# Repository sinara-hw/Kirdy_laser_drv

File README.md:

# Kirdy

Low Noise Precision Laser Diode Driver with Built-in TEC Temperature Controller  

## Power Input
| Parameter | Min | Typical | Max | Unit | Condition |
| --- | --- | --- | --- | --- | ---|
| Input Voltage | | 12 | | V | |
| Input Current | | | 2 | A|
| PoE Standard | |  PoE+ (802.3at) | | |

Note: TEC Output Current should be limited to ±2A when it is being powered via PoE(802.3af). Otherwise, Kirdy may malfunction.

## Laser Diode Driver
### Current Source Controller  
| Parameter | Min | Typical | Max | Unit | Condition |
| --- | --- | --- | --- | --- | ---| 
| Resolution | | 0.292 | | uA |
| Control Range| | | 307.2 | mA | |
| Current Limit | | 319. | | mA| |
| Compliance voltage | | > 4.928 | | V | |   
| Current Noise (@ 1 kHz) | | < 300 || pA / rt(Hz) | @ DC Bias: 300 mA, Load: 10 Ω Load|
| RMS Noise(10 Hz - 1 MHz) || < 300 | | nA | @ DC Bias: 300 mA, Load: 10 Ω Load| 
| Temperature Coefficient | | ±1 | | ppm/°C | @ DC Bias: 50 mA. Tested Temperature Range: 43-56 °C |

### Photodiode Input
| Parameter | Min | Typical | Max | Unit | Condition |
| --- | --- | --- | --- | --- | ---|
| Photocurrent Range | 0 | | 3.0 | mA | |
| Photocurrent Resolution | | 0.8 | | uA | |
| Bandwidth (-3 dB) | | 500 | | Hz | |

Note1: Circuit may be damaged if photodiode input current exceeds 3.0 mA. User can modify the circuit and reprogram the photodiode current monitor range via the given driver.

Note2: Photodiode operates in photovoaic mode.

### Low Frequency Modulation Input
| Parameter | Min | Typical | Max | Unit | Condition |
| --- | --- | --- | --- | --- | ---|
| Input Voltage | -1.0 | | 1.0 | V | |
| Input Impedance | | 50 or 43.4k | | ohm | Depends on Termination Switch Position |
| Bandwidth (-3 dB) | | 18 | | MHz | @Modulation Depth: 25 mA/V, Input : 1 Vp-p, DC Bias: 150 mA |

Note: Low Frequency Modulation Input can accept DC input to impose a DC offset to the output current.

## TEC Temperature Controller
### TEC Current Output
| Parameter | Min | Typical | Max | Unit | Condition |
| --- | --- | --- | --- | --- | ---|
| Resolution | | 22.9 | | uA | |
| Control Range (Powered via 12 V Barrel Jack) | -3.0 | | 3.0 | A | With Active Cooling |
| Control Range (Powered via PoE(802.3af)) | -2.0 | | 2.0 | A | |
| Compliance Voltage | | 4.3 |  | V | |
| Voltage Reading Resolution | | 3.22 | | mV | |
| Current Reading Resolution | |  2.0 | | mA | |

### TEC Voltage and Current Limit
| Parameter | Min | Typical | Max | Unit | Condition |
| --- | --- | --- | --- | --- | ---|
| Voltage Limit Settable Range| 0 | | 4.3 | V | |
| Voltage Limit Resolution | | 3.14 | | mV | |
| Current Limit Settable Range | -3.0 | | 3.0 | A | |
| Current Limit Resolution | |  1.57 | | mA | |

### NTC Thermistor Sensor
| Parameter | Min | Typical | Max | Unit | Condition |
| --- | --- | --- | --- | --- | ---|
| Resolution | | 0.01 | | mK | With 10 kohm NTC with 3950 B-Constant, 25°C T0 |
| Sampling Rate | | 16.67 | > 1k | Hz | |

Note: Actual Sampling Rate subjects to device operating conditions.

### Digital PID Temperature Controller
| Parameter | Min | Typical | Max | Unit | Condition |
| --- | --- | --- | --- | --- | ---|
| Temperature Stability | | < 1| | mk | Using supplied Kirdy Adapter with its copper plate installed. PID Parameters are obtained from Kirdy Autotune Algorithm. |

Note: Actual Temperature Stability subjects to the ambient environment conditions.

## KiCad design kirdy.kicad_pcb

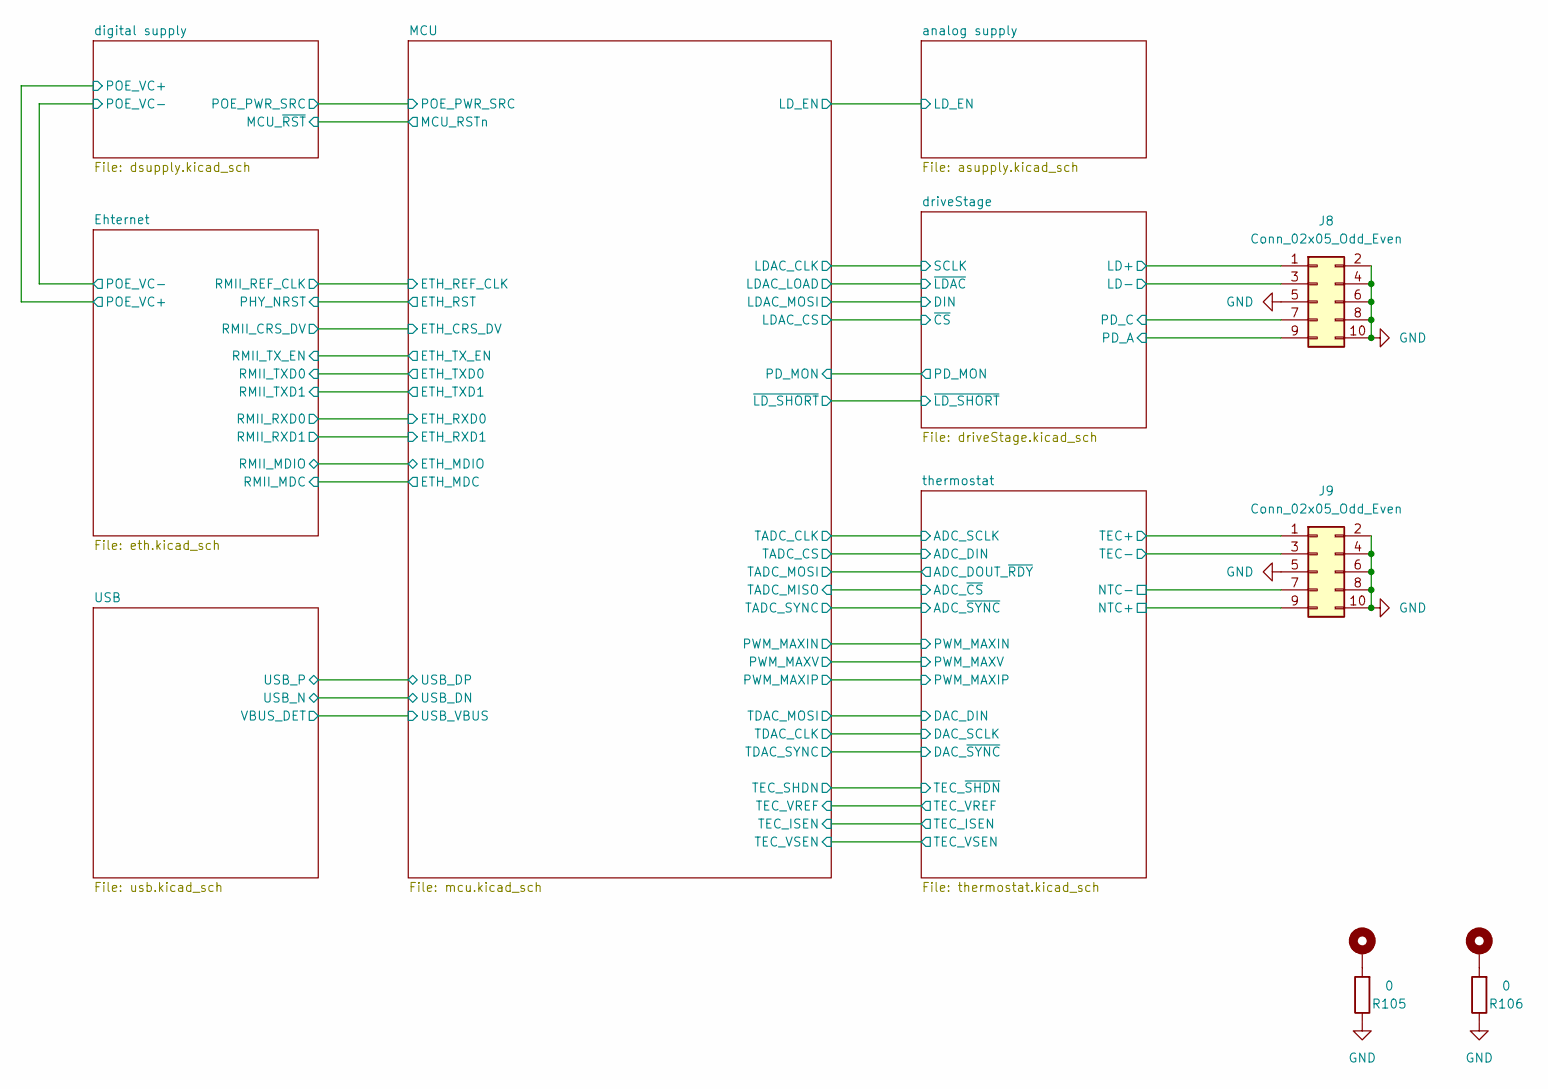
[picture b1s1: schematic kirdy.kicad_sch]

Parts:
H1, H2: MountingHole_Pad; MountingHole_2.7mm_M2.5_Pad_Via
J8, J9: Conn_02x05_Odd_Even; PinHeader_2x05_P2.54mm_Vertical_SMD; MFR_PN 3020-10-0300-00
R105, R106: 0; R_0603_1608Metric; MFR_PN RMCF0603ZT0R00

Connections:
+3.3VA: J8.7; also elsewhere on the board
+8V: J8.1; also elsewhere on the board
/driveStage/LD-: J8.3; also elsewhere on the board
/driveStage/PD_A: J8.9; also elsewhere on the board
/thermostat/NTC+: J9.9; also elsewhere on the board
/thermostat/NTC-: J9.7; also elsewhere on the board
/thermostat/TEC+: J9.1; also elsewhere on the board
/thermostat/TEC-: J9.3; also elsewhere on the board
GND: J8.2, J8.4, J8.5, J8.6, J8.8, J8.10, J9.2, J9.4, J9.5, J9.6, J9.8, J9.10, R105.1, R106.1; also elsewhere on the board
unnamed: H1.1, R105.2
unnamed: H2.1, R106.2

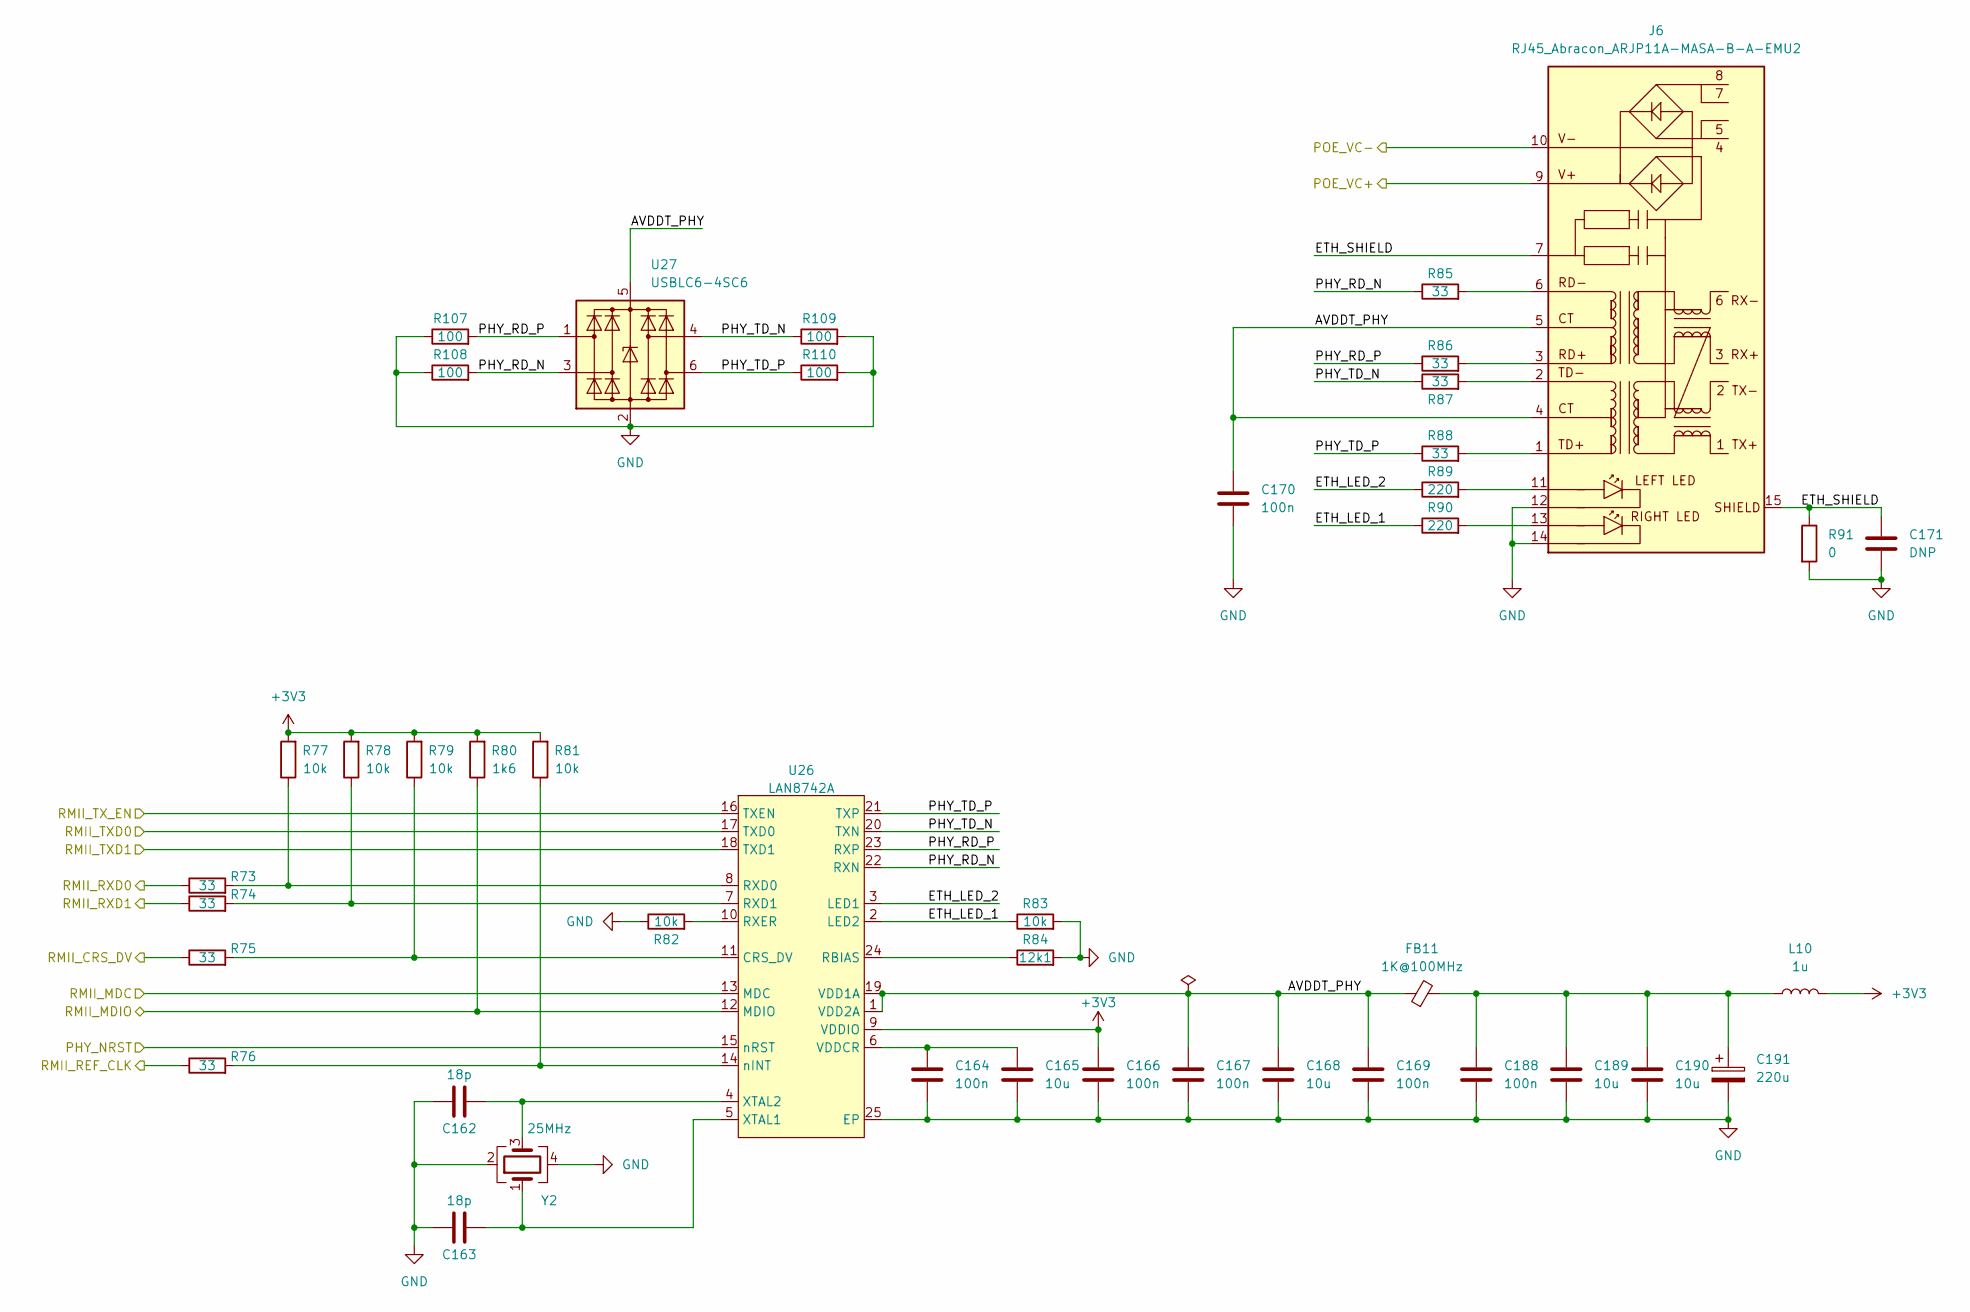
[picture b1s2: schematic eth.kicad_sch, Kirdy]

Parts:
C162, C163: 18p; C_0603_1608Metric; MFR_PN 0603N180J500CT
C164, C166, C167, C169, C170, C188: 100n; C_0603_1608Metric; MFR_PN CL10B104KB8NNWC
C165, C168, C189, C190: 10u; C_0805_2012Metric; MFR_PN CL21B106KOQNNNG
C171: DNP; C_1206_3216Metric; MFR_PN 12067C472KAT2A
C191: 220u; CP_EIA-7343-15_Kemet-W; MFR_PN T491D227K016AT
FB11: 1K@100MHz; L_1210_3225Metric; MFR_PN FBMH3225HM102NT
J6: RJ45_Abracon_ARJP11A-MASA-B-A-EMU2; RJ45_Abracon_ARJP11A-MA_Horizontal; MFR_PN ARJP11A-MASA-B-A-EMU2
L10: 1u; L_1008_2520Metric; MFR_PN DFE252012F-1R0M=P2
R73, R74, R75, R76, R85, R86, R87, R88: 33; R_0603_1608Metric; MFR_PN RC0603FR-0733RL
R77, R78, R79, R81, R82, R83: 10k; R_0603_1608Metric; MFR_PN RNCP0603FTD10K0
R80: 1k6; R_0603_1608Metric; MFR_PN RT0603FRE071K6L
R84: 12k1; R_0603_1608Metric; MFR_PN RNCP0603FTD12K1
R89, R90: 220; R_0603_1608Metric; MFR_PN WR06X2200FTL
R91: 0; R_0603_1608Metric; MFR_PN RMCF0603ZT0R00
R107, R108, R109, R110: 100; R_0603_1608Metric; MFR_PN RT0603FRE07300RL
U26: LAN8742A; QFN-24-1EP_4x4mm_P0.5mm_EP2.6x2.6mm; MFR_PN LAN8742A-CZ
U27: USBLC6-4SC6; SOT-23-6; MFR_PN USBLC6-4SC6Y
Y2: 25MHz; Crystal_SMD_2016-4Pin_2.0x1.6mm; MFR_PN FA-128 25.0000MF10Z-AC3

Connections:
+3V3: C166.1, L10.2, R77.2, R78.2, R79.2, R80.2, R81.2, U26.9 (VDDIO); also elsewhere on the board
/Ehternet/AVDDT_PHY: C167.1, C168.1, C169.1, C170.1, FB11.1, J6.4 (CT), J6.5 (CT), U26.1 (VDD2A), U26.19 (VDD1A), U27.5 (VBUS)
/Ehternet/ETH_LED_1: R83.1, R90.1, U26.2 (LED2)
/Ehternet/ETH_LED_2: R89.1, U26.3 (LED1)
/Ehternet/ETH_SHIELD: C171.1, J6.7, J6.15 (SHIELD), R91.1
/Ehternet/PHY_NRST: U26.15 (nRST); also elsewhere on the board
/Ehternet/PHY_RD_N: R85.1, R108.2, U26.22 (RXN), U27.3 (I/O2)
/Ehternet/PHY_RD_P: R86.1, R107.2, U26.23 (RXP), U27.1 (I/O1)
/Ehternet/PHY_TD_N: R87.1, R109.1, U26.20 (TXN), U27.4 (I/O3)
/Ehternet/PHY_TD_P: R88.1, R110.1, U26.21 (TXP), U27.6 (I/O4)
/Ehternet/POE_VC+: J6.9 (V+); also elsewhere on the board
/Ehternet/POE_VC-: J6.10 (V-); also elsewhere on the board
/Ehternet/RMII_CRS_DV: R75.1; also elsewhere on the board
/Ehternet/RMII_MDC: U26.13 (MDC); also elsewhere on the board
/Ehternet/RMII_MDIO: R80.1, U26.12 (MDIO); also elsewhere on the board
/Ehternet/RMII_REF_CLK: R76.1; also elsewhere on the board
/Ehternet/RMII_RXD0: R73.1; also elsewhere on the board
/Ehternet/RMII_RXD1: R74.1; also elsewhere on the board
/Ehternet/RMII_TXD0: U26.17 (TXD0); also elsewhere on the board
/Ehternet/RMII_TXD1: U26.18 (TXD1); also elsewhere on the board
/Ehternet/RMII_TX_EN: U26.16 (TXEN); also elsewhere on the board
GND: C162.1, C163.1, C164.2, C165.2, C166.2, C167.2, C168.2, C169.2, C170.2, C171.2, C188.2, C189.2, C190.2, C191.2, J6.12 (LLED-), J6.14 (RLED-), R82.1, R83.2, R84.2, R91.2, R107.1, R108.1, R109.2, R110.2, U26.25 (EP), U27.2 (GND), Y2.2, Y2.4; also elsewhere on the board
unnamed: C162.2, U26.4 (XTAL2), Y2.3
unnamed: C163.2, U26.5 (XTAL1), Y2.1
unnamed: C164.1, C165.1, U26.6 (VDDCR)
unnamed: C188.1, C189.1, C190.1, C191.1, FB11.2, L10.1
unnamed: J6.1 (TD+), R88.2
unnamed: J6.2 (TD-), R87.2
unnamed: J6.3 (RD+), R86.2
unnamed: J6.6 (RD-), R85.2
unnamed: J6.11 (LLED+), R89.2
unnamed: J6.13 (RLED+), R90.2
unnamed: R73.2, R77.1, U26.8 (RXD0)
unnamed: R74.2, R78.1, U26.7 (RXD1)
unnamed: R75.2, R79.1, U26.11 (CRS_DV)
unnamed: R76.2, R81.1, U26.14 (nINT)
unnamed: R82.2, U26.10 (RXER)
unnamed: R84.1, U26.24 (RBIAS)

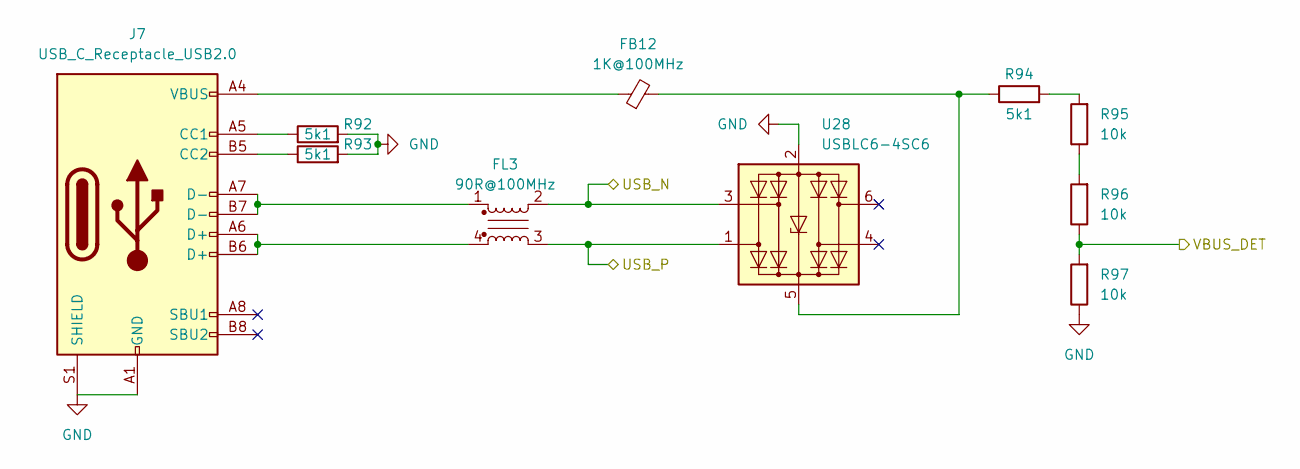
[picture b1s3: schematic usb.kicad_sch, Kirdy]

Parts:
FB12: 1K@100MHz; L_1210_3225Metric; MFR_PN FBMH3225HM102NT
FL3: 90R@100MHz; L_CommonModeChoke_Coilcraft_0603USB; MFR_PN 0603USB-222MLC
J7: USB_C_Receptacle_USB2.0; USB_C_Receptacle_HRO_TYPE-C-31-M-12; MFR_PN TYPE-C-31-M-12
R92, R93, R94: 5k1; R_0603_1608Metric; MFR_PN RMCF0603FT5K10
R95, R96, R97: 10k; R_0603_1608Metric; MFR_PN RNCP0603FTD10K0
U28: USBLC6-4SC6; SOT-23-6; MFR_PN USBLC6-4SC6Y

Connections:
/MCU/USB_DN: FL3.2, U28.3 (I/O2); also elsewhere on the board
/MCU/USB_DP: FL3.3, U28.1 (I/O1); also elsewhere on the board
/MCU/USB_VBUS: R96.1, R97.2; also elsewhere on the board
GND: J7.A1 (GND), J7.A12 (GND), J7.B1 (GND), J7.B12 (GND), J7.S1 (SHIELD), R92.2, R93.2, R97.1, U28.2 (GND); also elsewhere on the board
unnamed: FB12.1, J7.A4 (VBUS), J7.A9 (VBUS), J7.B4 (VBUS), J7.B9 (VBUS)
unnamed: FB12.2, R94.1, U28.5 (VBUS)
unnamed: FL3.1, J7.A7 (D-), J7.B7 (D-)
unnamed: FL3.4, J7.A6 (D+), J7.B6 (D+)
unnamed: J7.A5 (CC1), R92.1
unnamed: J7.B5 (CC2), R93.1
unnamed: R94.2, R95.2
unnamed: R95.1, R96.2

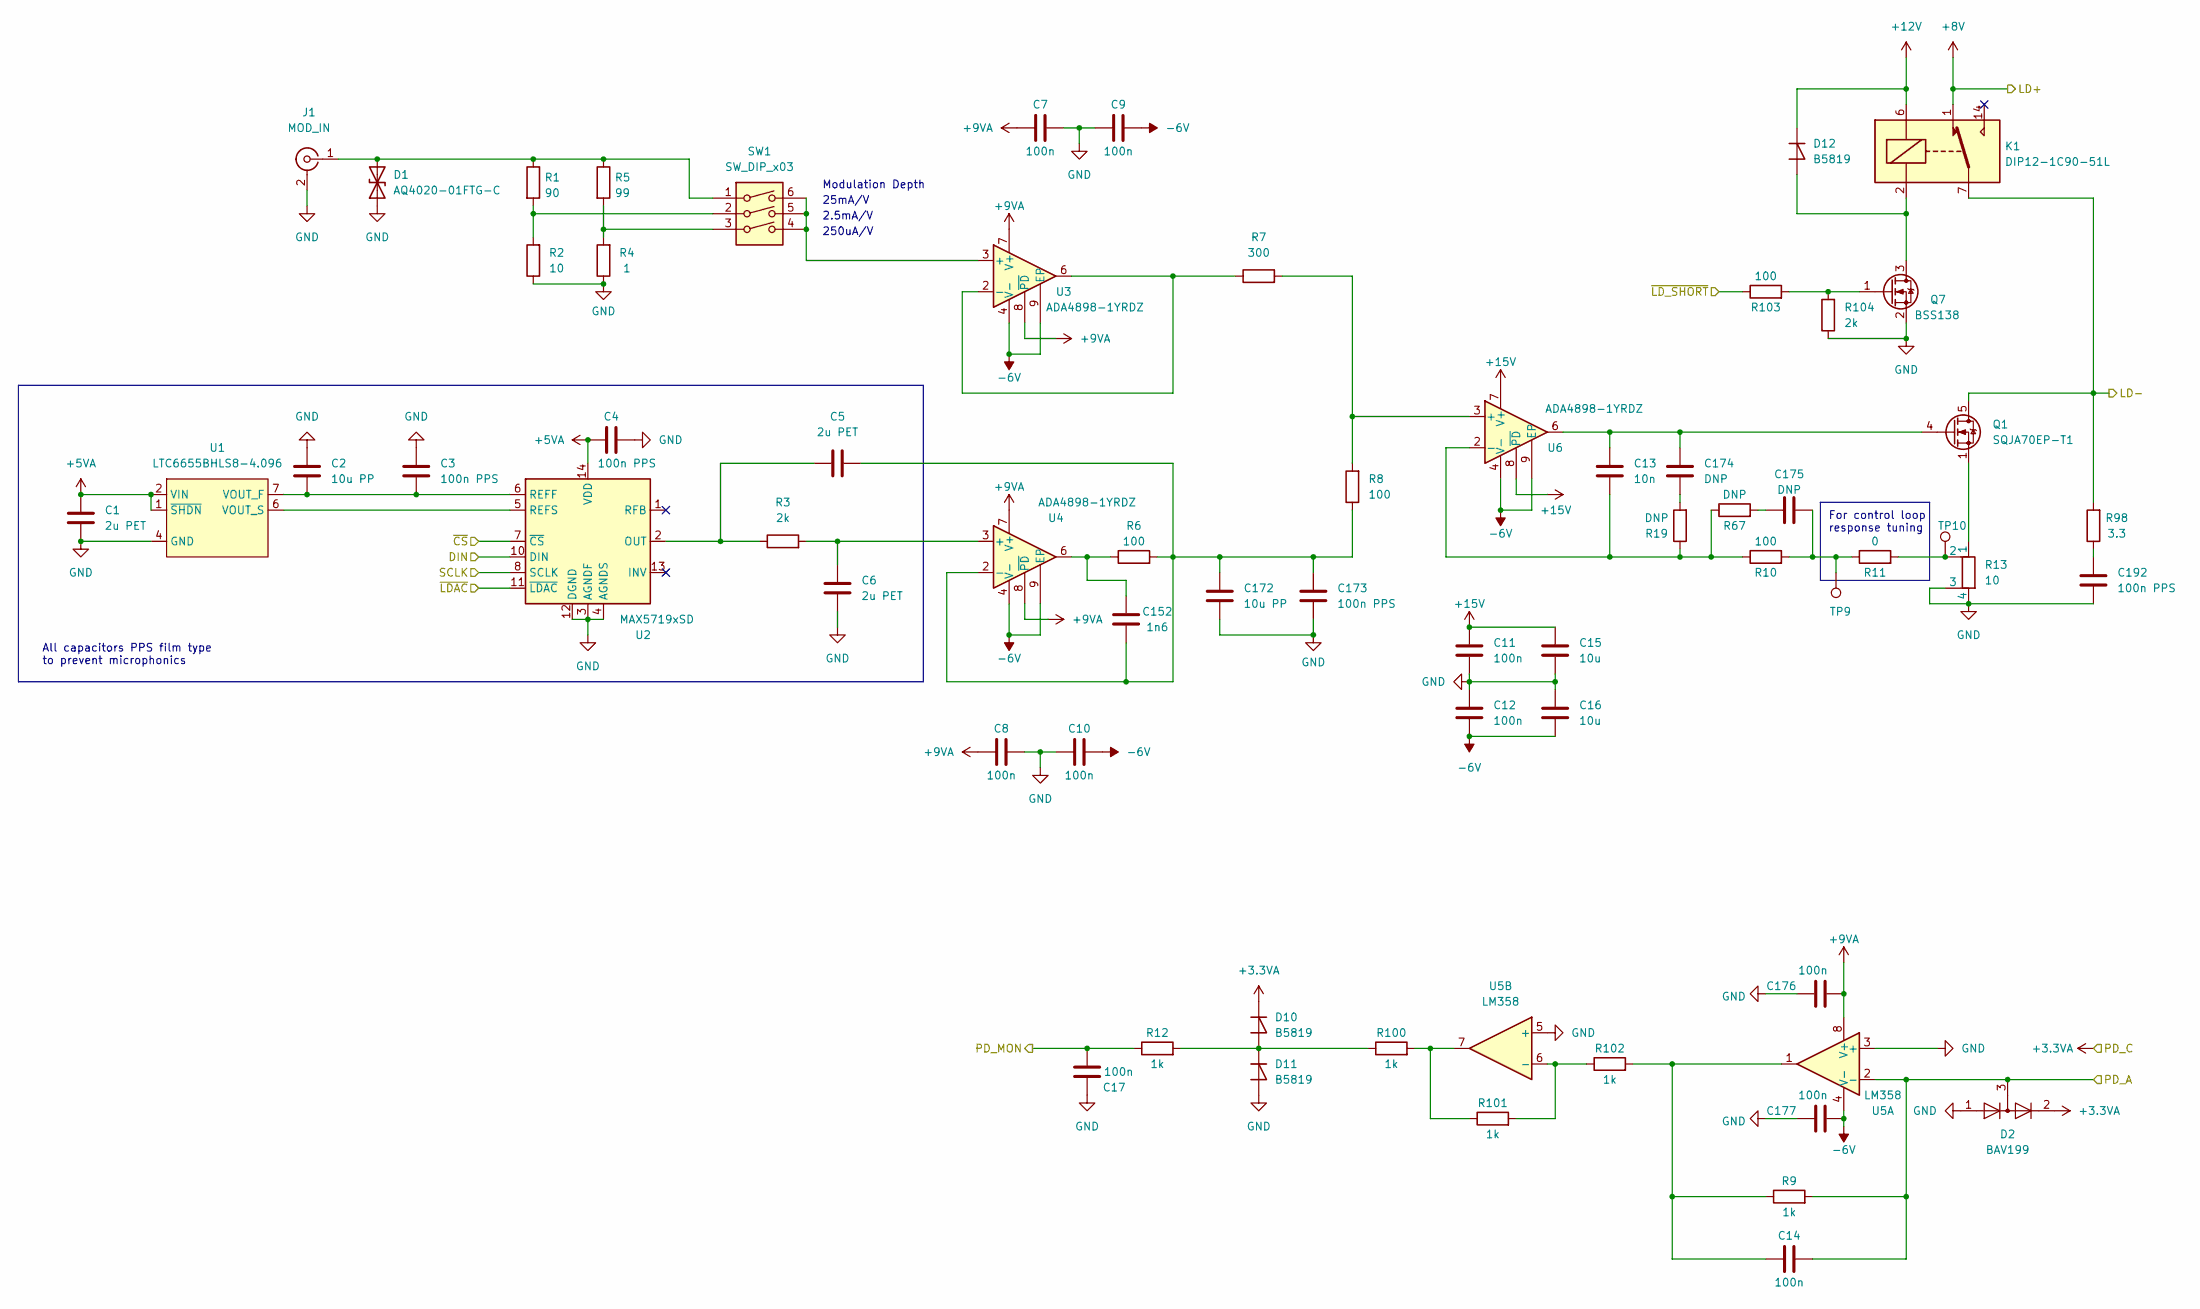
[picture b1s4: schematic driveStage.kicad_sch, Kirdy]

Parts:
C1, C5, C6: 2u PET; C_1812_4532Metric; MFR_PN 35MU225MC14532
C2, C172: 10u PP; C_1812_4532Metric; MFR_PN 16MU106MC44532
C3, C4, C173, C192: 100n PPS; C_1210_3225Metric; MFR_PN ECH-U1C104JX5
C7, C8, C9, C10, C11, C12, C17, C176, C177: 100n; C_0603_1608Metric; MFR_PN CL10B104KB8NNWC
C13: 10n; C_0603_1608Metric; MFR_PN 0603B103K500CT
C14: 100n; C_0603_1608Metric; MFR_PN GCM1885C1H162FA16D
C15, C16: 10u; C_0805_2012Metric; MFR_PN CL21B106KOQNNNG
C152: 1n6; C_0603_1608Metric; MFR_PN GCM1885C1H162FA16D
C174, C175: DNP; C_0603_1608Metric
D1: AQ4020-01FTG-C; D_SOD-323; MFR_PN AQ4020-01FTG-C
D2: BAV199; SOT-23; MFR_PN BAV199W-7
D10, D11, D12: B5819; D_SOD-323; MFR_PN B5819WS-TP
J1: MOD_IN; SMA_Amphenol_132203-12_Horizontal; MFR_PN 132203-12
K1: DIP12-1C90-51L; Relay_StandexMeder_DIP_LowProfile
Q1: SQJA70EP-T1; TDSON-8-1; MFR_PN SQJA70EP-T1_GE3
Q7: BSS138; SOT-23; MFR_PN BSS138W-TP
R1: 90; R_0603_1608Metric
R2: 10; R_0603_1608Metric; MFR_PN RT0603BRD0710RL
R3, R104: 2k; R_0603_1608Metric; MFR_PN RC0603FR-072KL
R4: 1; R_0603_1608Metric; MFR_PN ERJ-3RQF1R0V
R5: 99; R_0603_1608Metric
R6, R8: 100; R_0603_1608Metric; MFR_PN RT0603FRE07300RL
R7: 300; R_0603_1608Metric; MFR_PN WR06X1000FTL
R9, R12, R100, R101, R102: 1k; R_0603_1608Metric; MFR_PN RNCP0603FTD1K00
R10, R103: 100; R_0603_1608Metric; MFR_PN WR06X1000FTL
R11: 0; R_0603_1608Metric; MFR_PN RMCF0603ZT0R00
R13: 10; R_Shunt_VCS1625ZP; MFR_PN Y160610R0000D9W
R19, R67: DNP; R_0603_1608Metric
R98: 3.3; R_0603_1608Metric
SW1: SW_DIP_x03; SW_DIP_SPSTx03_Slide_Omron_A6S-310x_W8.9mm_P2.54mm; MFR_PN A6SN-3104
TP9, TP10: TestPoint; TestPoint_Pad_2.0x2.0mm
U1: LTC6655BHLS8-4.096; LCC127P500X500X155-8N; MFR_PN LTC6655BHLS8-4.096
U2: MAX5719xSD; SOIC-14_3.9x8.7mm_P1.27mm; MFR_PN MAX5719AGSD+
U3, U4, U6: ADA4898-1YRDZ; SOIC-8-1EP_3.9x4.9mm_P1.27mm_EP2.29x3mm; MFR_PN ADA4898-1YRDZ
U5: LM358; SOIC-8_3.9x4.9mm_P1.27mm

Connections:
+3.3VA: D2.2 (A), D10.1 (K); also elsewhere on the board
+5VA: C1.1, C4.1, U1.1 (~SHDN), U1.2 (VIN), U2.14 (VDD); also elsewhere on the board
+8V: K1.1; also elsewhere on the board
+9VA: C7.1, C8.1, C176.2, U3.7 (V+), U3.8 (~PD), U4.7 (V+), U4.8 (~PD), U5.8 (V+); also elsewhere on the board
+12V: D12.1 (K), K1.6; also elsewhere on the board
+15V: C11.1, C15.1, U6.7 (V+), U6.8 (~PD); also elsewhere on the board
-6V: C9.2, C10.2, C12.2, C16.2, C177.2, U3.4 (V-), U3.9 (EP), U4.4 (V-), U4.9 (EP), U5.4 (V-), U6.4 (V-), U6.9 (EP); also elsewhere on the board
/MCU/LDAC_CLK: U2.8 (SCLK); also elsewhere on the board
/MCU/LDAC_CS: U2.7 (~CS); also elsewhere on the board
/MCU/LDAC_LOAD: U2.11 (~LDAC); also elsewhere on the board
/MCU/LDAC_MOSI: U2.10 (DIN); also elsewhere on the board
/MCU/PD_MON: C17.2, R12.1; also elsewhere on the board
/MCU/~LD_SHORT: R103.1; also elsewhere on the board
/driveStage/LD-: K1.7, K1.8, Q1.5 (D), R98.2; also elsewhere on the board
/driveStage/PD_A: C14.2, D2.3 (K), R9.2, U5.2 (-); also elsewhere on the board
GND: C1.2, C2.1, C3.1, C4.2, C6.2, C7.2, C8.2, C9.1, C10.1, C11.2, C12.1, C15.2, C16.1, C17.1, C172.2, C173.2, C176.1, C177.1, C192.2, D1.1 (A1), D2.1 (K), D11.2 (A), J1.2 (Ext), Q7.2 (S), R2.1, R4.1, R13.3, R13.4, R104.1, U1.3 (GND), U1.4 (GND), U1.5 (GND), U1.8 (GND), U2.3 (AGNDF), U2.4 (AGNDS), U2.12 (DGND), U5.3 (+), U5.5 (+); also elsewhere on the board
unnamed: C2.2, C3.2, U1.7 (VOUT_F), U2.6 (REFF)
unnamed: C5.1, R3.1, U2.2 (OUT)
unnamed: C6.1, R3.2, U4.3 (+)
unnamed: C13.1, C174.1, Q1.4 (G), U6.6
unnamed: C13.2, R10.1, R19.1, R67.1, U6.2 (-)
unnamed: C14.1, R9.1, R102.2, U5.1
unnamed: C5.2, C152.1, C172.1, C173.1, R6.2, R8.1, U4.2 (-)
unnamed: C152.2, R6.1, U4.6
unnamed: C174.2, R19.2
unnamed: C175.1, R67.2
unnamed: C175.2, R10.2, R11.1, TP9.1
unnamed: C192.1, R98.1
unnamed: D1.2 (A2), J1.1 (In), R1.1, R5.1, SW1.1
unnamed: D10.2 (A), D11.1 (K), R12.2, R100.1
unnamed: D12.2 (A), K1.2, Q7.3 (D)
unnamed: Q1.1 (S), Q1.2 (S), Q1.3 (S), R13.1
unnamed: Q7.1 (G), R103.2, R104.2
unnamed: R1.2, R2.2, SW1.2
unnamed: R4.2, R5.2, SW1.3
unnamed: R7.1, U3.2 (-), U3.6
unnamed: R7.2, R8.2, U6.3 (+)
unnamed: R11.2, R13.2, TP10.1
unnamed: R100.2, R101.1, U5.7
unnamed: R101.2, R102.1, U5.6 (-)
unnamed: SW1.4, SW1.5, SW1.6, U3.3 (+)
unnamed: U1.6 (VOUT_S), U2.5 (REFS)

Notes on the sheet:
250uA/V
All capacitors PPS film type to prevent microphonics
2.5mA/V
For control loop response tuning
25mA/V
Modulation Depth

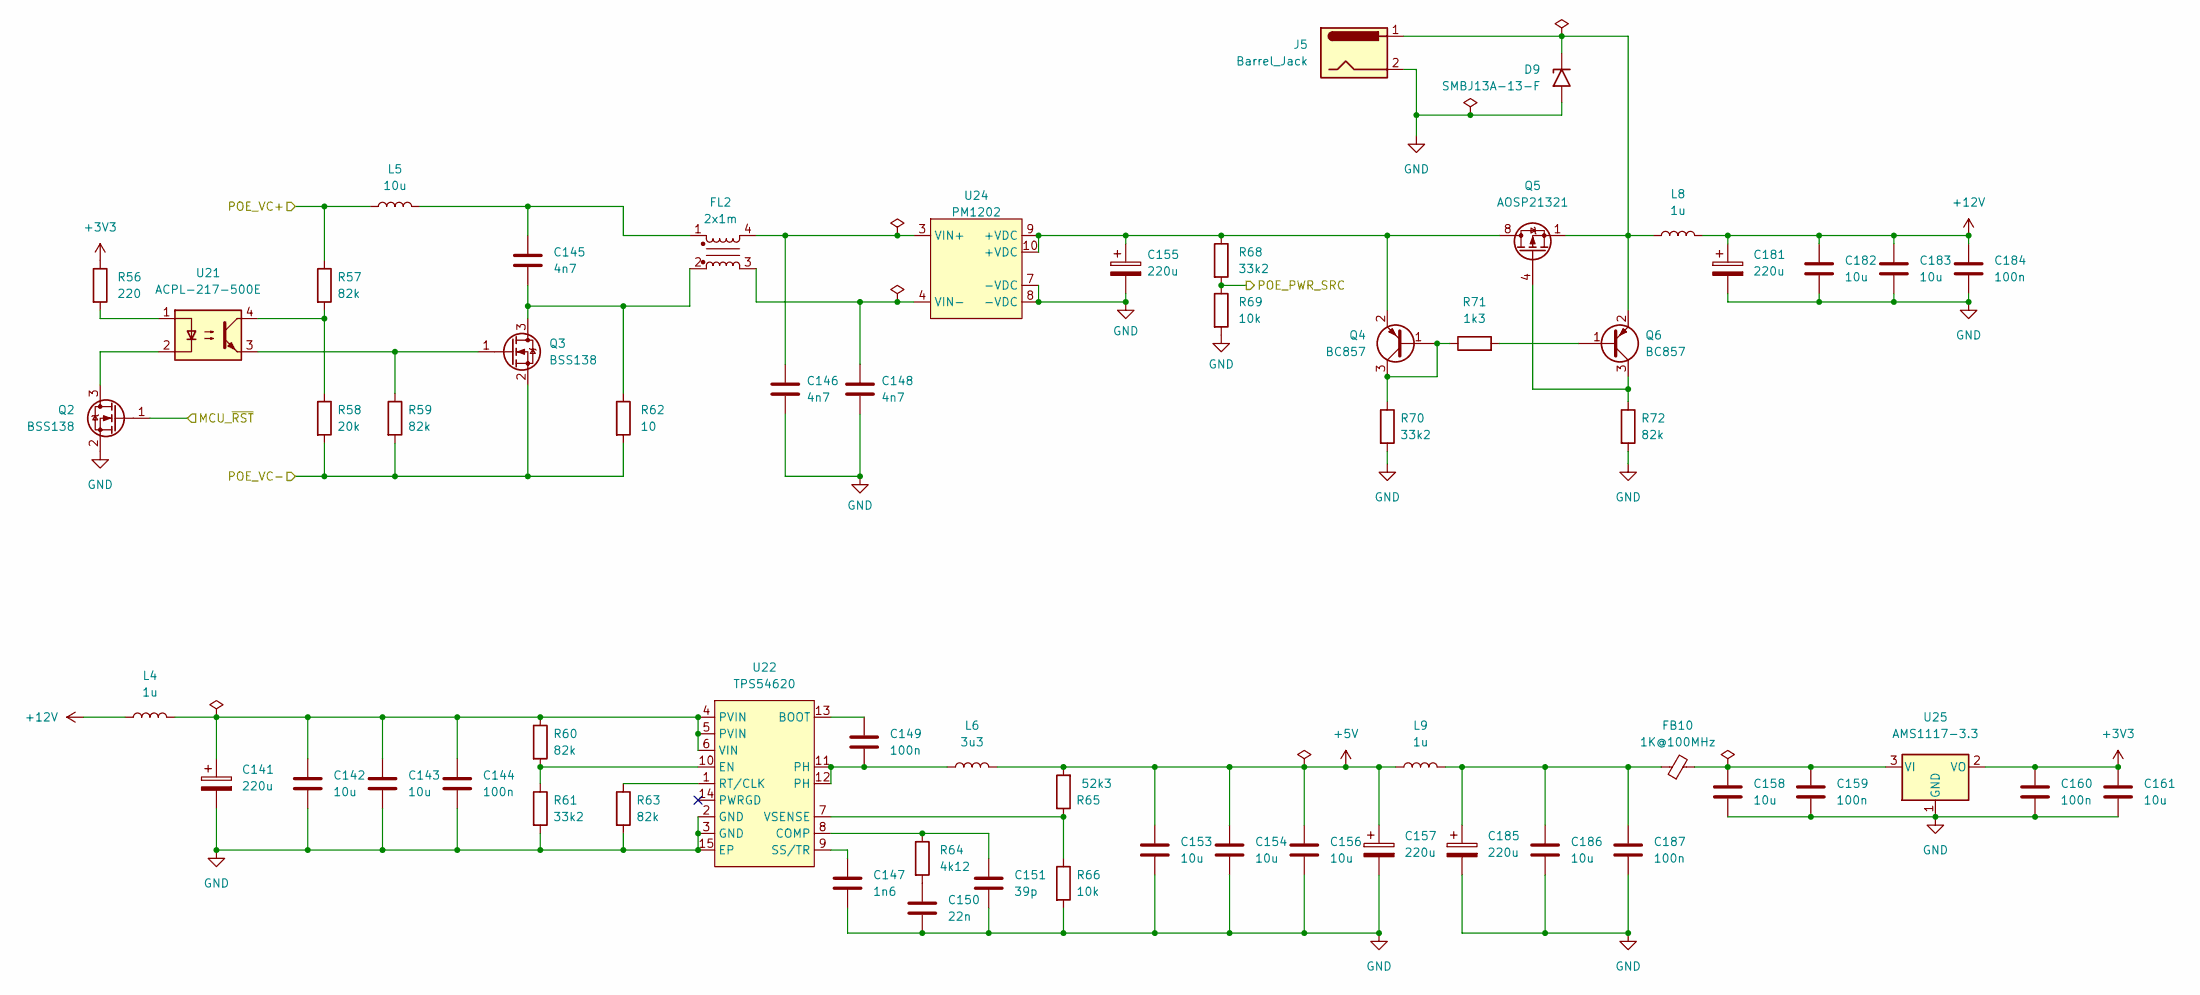
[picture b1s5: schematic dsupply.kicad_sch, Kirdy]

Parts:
C141, C155, C157, C181, C185: 220u; CP_EIA-7343-15_Kemet-W; MFR_PN T491D227K016AT
C142, C143, C153, C154, C156, C158, C161, C182, C183, C186: 10u; C_0805_2012Metric; MFR_PN CL21B106KOQNNNG
C144, C149, C159, C160, C184, C187: 100n; C_0603_1608Metric; MFR_PN CL10B104KB8NNWC
C145, C146, C148: 4n7; C_1206_3216Metric; MFR_PN 12067C472KAT2A
C147: 1n6; C_0603_1608Metric; MFR_PN GCM1885C1H162FA16D
C150: 22n; C_0603_1608Metric; MFR_PN 06035C223JAT2A
C151: 39p; C_0603_1608Metric; MFR_PN 0603N390J500CT
D9: SMBJ13A-13-F; D_SMB; MFR_PN SMBJ13A-13-F
FB10: 1K@100MHz; L_1210_3225Metric; MFR_PN FBMH3225HM102NT
FL2: 2x1m; L_CommonModeChoke_Wuerth_WE-SL5; MFR_PN 744273501
J5: Barrel_Jack; BarrelJack_CUI_PJ-063AH_Horizontal; MFR_PN PJ-063BH
L4, L8, L9: 1u; L_1008_2520Metric; MFR_PN DFE252012F-1R0M=P2
L5: 10u; L_Wuerth_WE-PD-Typ-LS; MFR_PN 74477110
L6: 3u3; L_Wuerth_MAPI-4020; MFR_PN 74438356033
Q2, Q3: BSS138; SOT-23; MFR_PN BSS138W-TP
Q4, Q6: BC857; SOT-23; MFR_PN BC857B-TP
Q5: AOSP21321; SOIC-8_3.9x4.9mm_P1.27mm; MFR_PN AOSP21321
R56: 220; R_0603_1608Metric; MFR_PN WR06X2200FTL
R57, R59, R60, R63, R72: 82k; R_0603_1608Metric; MFR_PN CRGCQ0603F82K
R58: 20k; R_0603_1608Metric; MFR_PN RMCF0603FT20K0
R61, R68, R70: 33k2; R_0603_1608Metric; MFR_PN CR0603-FX-3322ELF
R62: 10; R_0603_1608Metric; MFR_PN RT0603BRD0710RL
R64: 4k12; R_0603_1608Metric; MFR_PN RMCF0603FT4K12
R65: 52k3; R_0603_1608Metric; MFR_PN CR0603-FX-5232ELF
R66, R69: 10k; R_0603_1608Metric; MFR_PN RNCP0603FTD10K0
R71: 1k3; R_0603_1608Metric; MFR_PN RC0603FR-071K3L
U21: ACPL-217-500E; SMDIP-4_W7.62mm; MFR_PN EL3H7(C)(TA)-VG
U22: TPS54620; Texas_S-PVQFN-N14; MFR_PN TPS54620RHLR
U24: PM1202
U25: AMS1117-3.3; SOT-223-3_TabPin2; MFR_PN AMS1117-3.3

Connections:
+3V3: C160.1, C161.1, R56.1, U25.2 (VO); also elsewhere on the board
+5V: C153.1, C154.1, C156.1, C157.1, L6.2, L9.1, R65.2; also elsewhere on the board
+12V: C181.1, C182.1, C183.1, C184.1, L4.1, L8.2; also elsewhere on the board
/Ehternet/POE_VC+: L5.1, R57.1; also elsewhere on the board
/Ehternet/POE_VC-: Q3.2 (S), R58.2, R59.2, R62.2; also elsewhere on the board
/MCU/MCU_RSTn: Q2.1 (G); also elsewhere on the board
/MCU/POE_PWR_SRC: R68.2, R69.1; also elsewhere on the board
GND: C141.2, C142.2, C143.2, C144.2, C146.2, C147.2, C148.2, C150.2, C151.2, C153.2, C154.2, C155.2, C156.2, C157.2, C158.2, C159.2, C160.2, C161.2, C181.2, C182.2, C183.2, C184.2, C185.2, C186.2, C187.2, D9.2 (A2), J5.2, Q2.2 (S), R61.2, R63.2, R66.2, R69.2, R70.2, R72.2, U22.2 (GND), U22.3 (GND), U22.15 (EP), U24.7 (-VDC), U24.8 (-VDC), U25.1 (GND); also elsewhere on the board
unnamed: C141.1, C142.1, C143.1, C144.1, L4.2, R60.1, U22.4 (PVIN), U22.5 (PVIN), U22.6 (VIN)
unnamed: C145.1, FL2.1, L5.2
unnamed: C145.2, FL2.2, Q3.3 (D), R62.1
unnamed: C146.1, FL2.4, U24.3 (VIN+)
unnamed: C147.1, U22.9 (SS/TR)
unnamed: C148.1, FL2.3, U24.4 (VIN-)
unnamed: C149.1, U22.13 (BOOT)
unnamed: C149.2, L6.1, U22.11 (PH), U22.12 (PH)
unnamed: C150.1, R64.2
unnamed: C151.1, R64.1, U22.8 (COMP)
unnamed: C155.1, Q4.2 (E), Q5.5 (D), Q5.6 (D), Q5.7 (D), Q5.8 (D), R68.1, U24.9 (+VDC), U24.10 (+VDC)
unnamed: C158.1, C159.1, FB10.2, U25.3 (VI)
unnamed: C185.1, C186.1, C187.1, FB10.1, L9.2
unnamed: D9.1 (A1), J5.1, L8.1, Q5.1 (S), Q5.2 (S), Q5.3 (S), Q6.2 (E)
unnamed: Q2.3 (D), U21.2
unnamed: Q3.1 (G), R59.1, U21.3
unnamed: Q4.1 (B), Q4.3 (C), R70.1, R71.1
unnamed: Q5.4 (G), Q6.3 (C), R72.1
unnamed: Q6.1 (B), R71.2
unnamed: R56.2, U21.1
unnamed: R57.2, R58.1, U21.4
unnamed: R60.2, R61.1, U22.10 (EN)
unnamed: R63.1, U22.1 (RT/CLK)
unnamed: R65.1, R66.1, U22.7 (VSENSE)

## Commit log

2022-06-09 Update 'README.md'
2022-06-12 add project
2022-06-12 add symbol and footprint lib
2022-06-13 add driver stage sch
2022-06-13 minor improvements
2022-06-13 add ref dac
2022-06-14 finish drive stage, add sheets
2022-06-15 remove ref dac sheet, finish thermostat
2022-06-15 add TEC V sense, filter TEC I sense
2022-06-15 polish
2022-06-16 before beer
2022-06-16 analog supply complete
2022-07-02 add PoE
2022-07-02 complete digital supply
2022-07-02 add ethernet
2022-07-03 add USB
2022-07-03 add MCU basic connections
2022-07-03 add STM32CubeMX file for pin planning
2022-07-03 complete mcu
2022-07-04 first draft complete
2022-07-04 Complete BOM, FP assignment
2022-07-04 cleanup
2022-07-04 rough placement
2022-07-04 add bom, finish rough placement
2022-07-05 complete placement
2022-07-06 routing, bom update
2022-07-06 more routing
2022-07-06 roughly done
2022-07-06 passes DRC
2022-07-07 shove trace
2022-07-07 minor adjustments
2022-08-04 add V01 production files, bug fixes
2022-08-18 v 0.2 schematics
2022-08-18 fixes
2022-08-19 compensation
2022-08-19 add gate pull down
2022-08-20 remove rev resistors
2022-08-20 change damper
2022-08-20 change PD LD circuit
2022-08-20 change diodes
2022-08-22 change LD shorting circuit
2022-08-25 v2 schematics, fp assignment
2022-08-25 import sch to pcb
2022-08-31 sync
2022-09-03 fix eth
2022-09-04 placement v2
2022-09-04 update palcement
2022-09-05 some layout
2022-09-07 finish v2 layout
2022-09-07 clean up
2022-09-09 improve relay power circuitry
2023-10-12 Mirgrate to kicad7
2023-10-12 sch: R13 Power Resistor change to PDY10R000F
2023-10-25 pcb: migrate to kicad 7
2023-10-25 sch: Fix Issue #15
2023-10-25 sch: Add soft start to 12V PWR Jack input
2023-10-25 sch: Fix Issue #14
2023-10-25 sch: correct ethernet phy sigs connections to ESD - Pull up eth signals with 100R instead of pull down
2023-10-25 footprint: Correct PM1202 footprint - enlarge courtyard and silkscreen to reflect the clearance requirement so that it can be fully seated onto the PCB
2023-10-25 sch: LD DAC add parallel Cap to output resistor - Increase the Mod_In Signal Bandwidth - See Issue #22
2023-10-25 sch: Do not pass MCU RST to ETH - D3 -> DNP
2023-10-25 sch: Set DNP for DNP components
2023-10-25 sch: Add REF3033 for MCU ADC VREF
2023-10-25 sch: Support Temp ADC in alternate footprint - Issue #12 - Add Alternate AD7172-4BCPZ circuitry, symbol, footprint and 3D model
2023-10-25 sch: Tune LD- Out Series RC Network - R98 3R3 -> 10R - C192 100n PPS -> DNP - Add C199 2n2 in parallel C192
2023-10-25 sch: Use TL082 for PD_Mon TIA and LPF Stage
2023-10-25 sch: Tune the LD V-I Output Stage Feedback Network - R67 -> 0R - C175 -> 100pF
2023-10-25 sch: Modify dsupply freq_comp network - See Issue #21
2023-10-27 sch: Change PoE RJ45 Jack and change PM1202 Symbol - Use the same PoE RJ45 as sinara-hw thermostat - Add PM1202 Power input pins (VB+, VB-) - Remove PoE softstart circuit as PM1202 has inrush current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
2023-10-27 sch: Correct SWD Header MF/PN and Update Footprint - Use Adafuit 4048 Mini SWD Headers - Silkscreen is modified to indicate orientation of the header
2023-10-27 sch: Add redundant 2.54mm SWD Header
2023-10-30 sch: Correct typos in TEC_~{SHDN} ports
2023-10-30 sch: add lpf at TEC_VSEN Buffer Output
2023-10-30 sch: fix Temperature ADC SPI Connections - Fix Issue #25
2023-10-30 symbol: AD7172-4 sets DNC pin to unconnected type
2023-10-31 symbol: correct RJ45 VC output pin type - from power input to power output
2023-10-31 sch: correct POE_VC* pins name case - PoE_VC* -> POE_VC*
2023-10-31 sch: Update power related flags and nets symbols - Update the symbol from the kicad 7 built-in library - Remove ERC warnings
2023-10-31 footprint: Add TL082Hx TI SOIC-8 footprint
2023-11-02 pcb: Finish Layout for rev0_3 - Assign MFR_PN for all Components - schematics changes: - drivestage: Add Switch to optionally enable Modulation Signal Termination - Add alternate Precision Power Resi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
2023-11-08 thermostat: Fix wrong P/N in TEC Current Sense Res - Fix Issue #26
2023-11-08 sch: Fix incorrect TEC polarity in thermostat - Fix Issue #27
2023-11-08 pcb: Fix TEC Polarity Connections to Header - Fix Issue #27
2023-11-08 pcb: Remove "designed by" silkscreen
2023-11-09 sch, pcb: exclude MHs and soldering JP from BOM
2023-11-10 scripts: Add scripts to generate production files - The following files can be generated from the script. 1. Zipped(Gerber, Drill, Drill Map) 2. Bom, 3. Component Placement 4. Schematics PDF 5. Step 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
2023-11-10 sch: Update Title Block Info - rev0.3 -> rev0_3 - Correct the title of each schematics - Update the modified time
2023-11-10 Remove old production files
2023-11-10 sch, pcb: Correct MFR/PN and optimize BOM
2023-11-10 pcb: Add 3D Models
2023-11-15 Add Front Panel, Kirdy LD Adapter 3D models - Update sch, pcb, sym lib, footrprint lib - Position of Kirdy LD Adapter is relocated so that it is symmetric
2023-11-15 pcb: relocate switches for better accessibility - modulation depth SW and termination SW are relocated
2023-11-17 sch, pcb: Add mounting holes for Kirdy LD Adapter
2023-11-17 Port front panel markings design to Kicad - Front panel text markings can now be modified with Kicad
2023-11-21 drc: Check PWR nets clearance on pri and sec sides - Pri: PoE PWR nets - Sec: PWR nets like GND, 3V3 etc
2023-11-21 sch, pcb: Add PWR, POE_PWR netclasses
2023-11-21 3D_Model: Update 204-121ST
2023-11-27 Add Front Panel FreeCAD Assembly - Static Handle - PCB Brackets - Kirdy Front Panel Cutout
2023-11-27 Add: Footprints and Step Model for Caps - SMD ELEC: 865080345012 - SMD C0G Ceramic GRMJN65C1H104JE01J
2023-11-27 sch, pcb: Change kirdy LD adpter connectors - Add two extra mounting holes for kirdy LD adapter - Update kirdy LD adapter 3D model - Update the PCB layout accordingly
2023-11-27 sch, pcb: Remove X7R, X5R at input LT304x - Reduce the number of Tantalum Capacitor Used - Replace some non critical ones with Electrolytic Caps
2023-11-27 sch, pcb:Edit PCB shape for connectors to protrude - Connectors now protrude the front panel - Align the connectors by the outline generated from 3D Model - Update the front panel symbol to include t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
2023-11-27 sch, pcb: add 0R for TEC Vref Ouput - For debugging if needed
2023-11-27 sch, pcb: Add LPF and Buffer for TEC VREF
2023-11-27 sch, pcb: add tantalum C0G Caps for 8V out LT3045
2023-11-27 pcb: Add reference designators for connectors, SWs - SMA Connector, USB Type C, Power Jack, RJ45 - MCU Programming Headers and Boot 0 Headers - Termination Resistor SW, Modulation Depth SW
2023-11-27 sch, pcb: Replace FB of -6V +15V LDO with inductor - Build a Pi LPF on the input side
2023-11-27 sch, pcb: Add LEDs and TPs to Critical Power Rails
2023-11-27 sch, pcb: Add alternate footprint for LTC6655 Vref
2023-11-28 sch, pcb: Add 12V & Mounting holes to MCU EXT HDR
2023-11-28 Scripts: Comment Filed is included in the BOM
2023-11-28 3D: Update 3D models of KIrdy LD Adapter
2023-11-28 Cleanup and Update Modification Date
2023-11-29 sch: Add Mounting Screw Symbol and MFR/PN
2023-11-29 Reassign Reference Designators for all Symbols
2023-11-29 Scripts: Grab correct KICAD7_3DMODEL_DIR now - Todo: Use default.nix or flake.nix to setup the path
2023-11-29 sch, pcb: Add TAN Caps to all LT304x SET Pin - Prevent noise due to microphonics to be amplified by internal Amp - Remove the input TAN Caps as LT304x PSRR is very good - Replace TAN Caps in the 12V 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
2023-11-29 Add Front Panel MFR_PN
2023-11-29 Add Manufacturer into PM1202's Value & Comment
2023-11-30 sch: Add install Instructions for Power Resistor
2023-11-30 pcb: Relocate programming hdrs to an accessible place - Even after the MCU EXT mezzanine is installed
2023-11-30 pcb: Add GND and via fencing for Mod_IN signal
2023-11-30 sch: Correct Front Panel Kit MRF/PN & Value typo
2023-11-30 pcb: relocate programming hdrs - prev locations block Internal SMA cable
2023-11-30 Front Panel: Relocate markings to diff layers - Move the markings to different layers for generating prod docs - Add comments in the drawings pdf
2023-11-30 sch: Not to include TPs in BOM. Add prod comments - LTC6655 Vref adds production comments
2023-11-30 pcb: Update PN and properties of symbols
2023-12-13 Add Front Panel Mechanical Design and Drawings - Complete the Assembly in FreeCAD - Add Technical Drawings, Assembly Drawings, 3D model for production - Update text markings on KiCad
2023-12-13 sch: Set the mcu 2.54mm Prog HDR to be placed
2023-12-13 sch: Update PN and Comments
2023-12-13 pcb: Update clearance rules for JLCPCB manufacturing - No layout is changed. Only copper clearance and width are modified.
2023-12-13 sch: Add JLCPCB M3 x 8 Screws PN
2023-12-13 sch: Place Y169010R Power Resistor - cannot find purchasable PDY10R000F Power Resistor
2023-12-13 pcb: Update Front Panel 3D Model
2023-12-13 sch: Specify AD5680 MFR_PN to be -1 variant
2023-12-13 Add copper plate to LD Adapter 3D model
2023-12-13 flake: Generate prod files with flake.nix - Generate production files with nix build .
2023-12-13 sch: Add SMA Jack to Plug Cable to BOM - Internal SMA cable connecting LD adapter and Front Panel
2023-12-13 sch, pcb: correct polarity of LT3094xMSE C_Set
2023-12-13 Correct graphical mistakes in LTC3261 symbol - no functional changes
2023-12-13 PCB: Correct Y169010R0000T9L Footprint - Add more space between the pin holes and resistor body
2023-12-18 sch, pcb: Add TDAC_VFB. Change 2u2 PMLCAP P/N - Connect TDAC voltage output through a RC LPF to MCU PC0(ADC123_IN10) - 2u2 PMLCAP P/N is changed to 16V version instead of 35V for lower cost
2023-12-18 update flake: KiCAD_BOM_Generator
2023-12-19 sch, pcb: Add 0R to use TEC_VREF to bias TEC_VSEN - Optional
2023-12-19 sch, pcb: Correct opamp input polarity of TEC_VSEN - +ve IN connects to TEC+ - -ve IN connects to TEC-
2023-12-21 flake: Create TMP dir and use it for $HOME PATH
2023-12-30 flake: update dependencies
2023-12-30 flake: cleanup tmpdir management
2024-01-24 sch: correct MFR/PNs for BSS138, TLV9001, TPS54620
2024-01-30 sch: Add M3 Washer to BOM
2024-02-05 Panel: Add Mounting Plates for Fiber Optic Adapters
2024-02-06 bom: update MFR_PN and descriptions of SMA Cable
2025-02-26 Update README with Electrical Specs
2025-02-26 Readme: Fix formatting and add desc to LF Mod Input
2025-03-04 Update Power input requirement - Please refer to test result in Issue #55
2025-03-04 README: Update Compliance voltage
2025-03-04 README: 802.11 -> 802.3
2025-06-24 Fix issiues from lis, see bug/issiue list in DOC directory
